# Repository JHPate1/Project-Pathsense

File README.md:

# PathSense

> Autonomous spatial awareness for the visually impaired. A light-weight, intelligent, vest-wearable vision for your environment.
(Tracked Via LAPSE)
https://stardance.hackclub.com/projects/27167
---

# WHAT IT IS

PathSense is a wearable computer vision navigation vest (HOLY JUMBLE OF WORDS) intended to provide users with a more confidence-gaining awareness of their surroundings. With a powerful Raspberry Pi 5 in its core, and a combined network of precise distance sensors and tactile & audio feedback, this vest allows individuals with any level of vision to traverse indoor and outdoor spaces alike.

(Note the hook on the back will be made with a type of plastic that bends in so it will behave more like a clip)
(I do not know the name of the plastic yet)

---

# HOW IT WORKS

Essentially, PathSense is a complex, sensor-fused computer vision system rather than having one single sensor that dictates what is occurring in an environment, it combines and merges data from multiple inputs, checking for consistency and using the interpreted data in a reliable way.

# THE SENSORS

For this system, we have established a network of:

- 4 Time-of-Flight (ToF) sensors: To continuously determine precise distances in 3 directions of the space around the user, to a range of 4 meters.

- an AI Camera: To assess higher level object detection of hazards, landmarks, obstacles and the immediate surrounding terrain.

- GPS Module: To provide general global location awareness, including basic route following and orientation in city blocks and street space awareness including side walk identification.

The raw output from these sensors is sent to the custom written Python backend which interprets things real time.

---
## System Architecture
```
+-------------------------------------+
|    Raspberry Pi 5                   |
+--------------+----------------------+
               |
    +----------+----------+
    |          |          |
+---v---+  +---v---+  +---v---+
| 4x ToF|  |AI Cam |  |  GPS  |
|Sensor |  | Feed  |  |Module |
+---+---+  +---+---+  +---+---+
    |          |          |
    +----------+----------+
               |
    +----------v----------+
    |  Custom Python Core |
    |  (Sensor Fusion &   |
    |   Decision Logic)   |
    +----------+----------+
               |
    +----------+----------+
    |          |          |
+---v---+            +---v---+
|3x     |            |Audio  |
|Haptic |            |Engine |
|Lines  |            |       |
+-------+            +-------+
```
---

---

## Core Subsystems

### Spatial Distance Mapping
Four ToF sensors continuously monitor the environment for physical boundaries. They track distances to nearby walls, furniture, curbs, and other obstacles, giving the system a raw but reliable depth map of what is directly around you.

### Contextual Computer Vision
The camera feed runs an object detection model (YOLO) that adds meaning to the raw distance data. It can tell the difference between a person and a pole, identify an upcoming staircase, or flag uneven terrain. This contextual layer is what turns numbers into useful information.

### Dynamic Ground Navigation
When you are outdoors, the GPS module works alongside the camera to evaluate ground layouts, identify sidewalk edges, and avoid rocky or uneven paths.

### Dual Channel Feedback
Spatial data is translated into vibrations across three haptic motors. The intensity and location of each pulse tell you where to go and what to avoid. When something needs your immediate attention, like a sudden drop or an oncoming cyclist, the audio engine cuts in with a clear and sharp voice alert along with the activation of all haptic motors.

---

## Smart Sensor Arbitration

Wearable sensor arrays have a classic problem: false positives caused by normal human movement. Walking swings your arms. Eating brings your hands near your chest. Without intelligence, these motions would trigger constant, useless alerts. PathSense solves this by treating the camera as the primary source of truth. When you move your arms into the sensor path, the object detection model recognizes your hands in real time. The Python core then automatically suppresses data from any ToF sensors that are currently blocked. The result: no false positives.

---

## Custom Hardware: The Pi 5 HAT

PathSense uses a custom designed Raspberry Pi 5 expansion HAT to keep the wearable robust and wearable friendly.

- Interface Consolidation: All GPIO pins are mapped to dedicated, keyed JST connector sockets. Every sensor, motor, and module plugs in cleanly and allows for easy repairs.
- Vibration Resistant Design: The connectors and layout are built to stay reliable even while you are walking, running (not recommended yet), or navigating bumpy terrain.
- Neat Form Factor: No loose wires, no breadboards, no cable spaghetti. Just a clean, integrated stack that fits comfortably inside the vest.

---

## Bill of Materials (BOM)

### Purchased Components

| Ref    | Component                              | Description                                                                                         | Qty | Unit Price            | Total        |
| ------ | -------------------------------------- | --------------------------------------------------------------------------------------------------- | --- | --------------------- | ------------ |
| RPI5   | Raspberry Pi 5/2GB                     | Raspberry Pi 5 Single Board Computer, 2GB RAM                                                       | 1   | \$65.00               | \$65.00      |
| TOF    | TOF400C VL53L1X                        | 4M Laser Ranging Sensor Module, TOF Time-of-Flight Distance, IIC Output, 4pcs                       | 1   | \$21.89               | \$21.89      |
| WIRE   | Fermerry 22AWG Stranded Wire           | 22AWG Stranded Wire Spool, 10ft Each, 6 Colors, Flexible Silicone Hook up Wire Kit, Tinned Copper   | 1   | \$12.29               | \$12.29      |
| GPS    | NEO-6M GPS Module                      | GPS Module Receiver, Navigation Satellite Positioning, with Antenna, High Sensitivity               | 1   | \$9.99                | \$9.99       |
| VEST   | JKSafety Hi Vis Reflective Safety Vest | Hi Vis Reflective Safety Vest with Pockets, Mesh Fabric, Construction Safety Apparel, Black, Size L | 1   | \$9.99                | \$9.99       |
| HAPTIC | HilBeliFU Vibration Motor Module       | DC5V 9000RPM Vibration Motor Module, PWM Control, for DIY/Wearable Smart Device, 3pcs               | 1   | \$7.65                | \$7.65       |
| CAM    | Arducam 5MP Camera for Raspberry Pi    | 5MP OV5647 Camera Module V1, 1080P HD, for Raspberry Pi 5/4/3/3B+                                   | 1   | \$6.99                | \$6.99       |
| PSU    | Raspberry Pi 5 Power Supply            | PD Adapter USB C, 5V 5A Power Adapter for Raspberry Pi 5                                            | 1   | \$11.99               | \$11.99      |
| CONN   | JST-XH 2.54mm Connector Kit            | 460Pcs JST-XH Connector Kit, 2.54mm Male/Female 2/3/4/5/6Pin Header Housing, Terminal Wires         | 1   | \$7.58                | \$7.58       |
|        |                                        |                                                                                                     |     | **Subtotal**          | **\$153.37** |
|        |                                        |                                                                                                     |     | **Shipping (Pishop)** | **\$11.51**  |
|        |                                        |                                                                                                     |     | **Shipping (Amazon)** | **\$0.00**   |
|        |                                        |                                                                                                     |     | **Tax (Pishop)**      | **\$3.45**   |
|        |                                        |                                                                                                     |     | **Tax (Amazon)**      | **\$4.69**   |
|        |                                        |                                                                                                     |     | **TOTAL**             | **\$173.02** |

### PCBWay

| Ref | Component | Description | Qty | Unit Price | Total |
|-----|-----------|-------------|-----|------------|-------|
| PCB | Custom Pi 5 HAT PCB | 2 layer, HASL finish, 1.6mm FR4 | 5 | $4.10 | $20.50 |

**Subtotal (PCBWay):** $FREE (grant)

### PCB Parts On Hand
All Pi Hat Connectors
**Subtotal (On Hand):** $0.00

### Cost Summary

| Category | Amount |
|----------|--------|
| Purchased Components | $173.02 |
| PCBWay (Custom HAT) | $00.00 |
| **Grand Total** | **$173.02** |

---

## Built With

- Raspberry Pi 5
- Python
- Time of Flight (ToF) distance sensors
- AI powered object detection
- Custom PCB HAT design
- Haptic motor drivers
- GPS positioning modules

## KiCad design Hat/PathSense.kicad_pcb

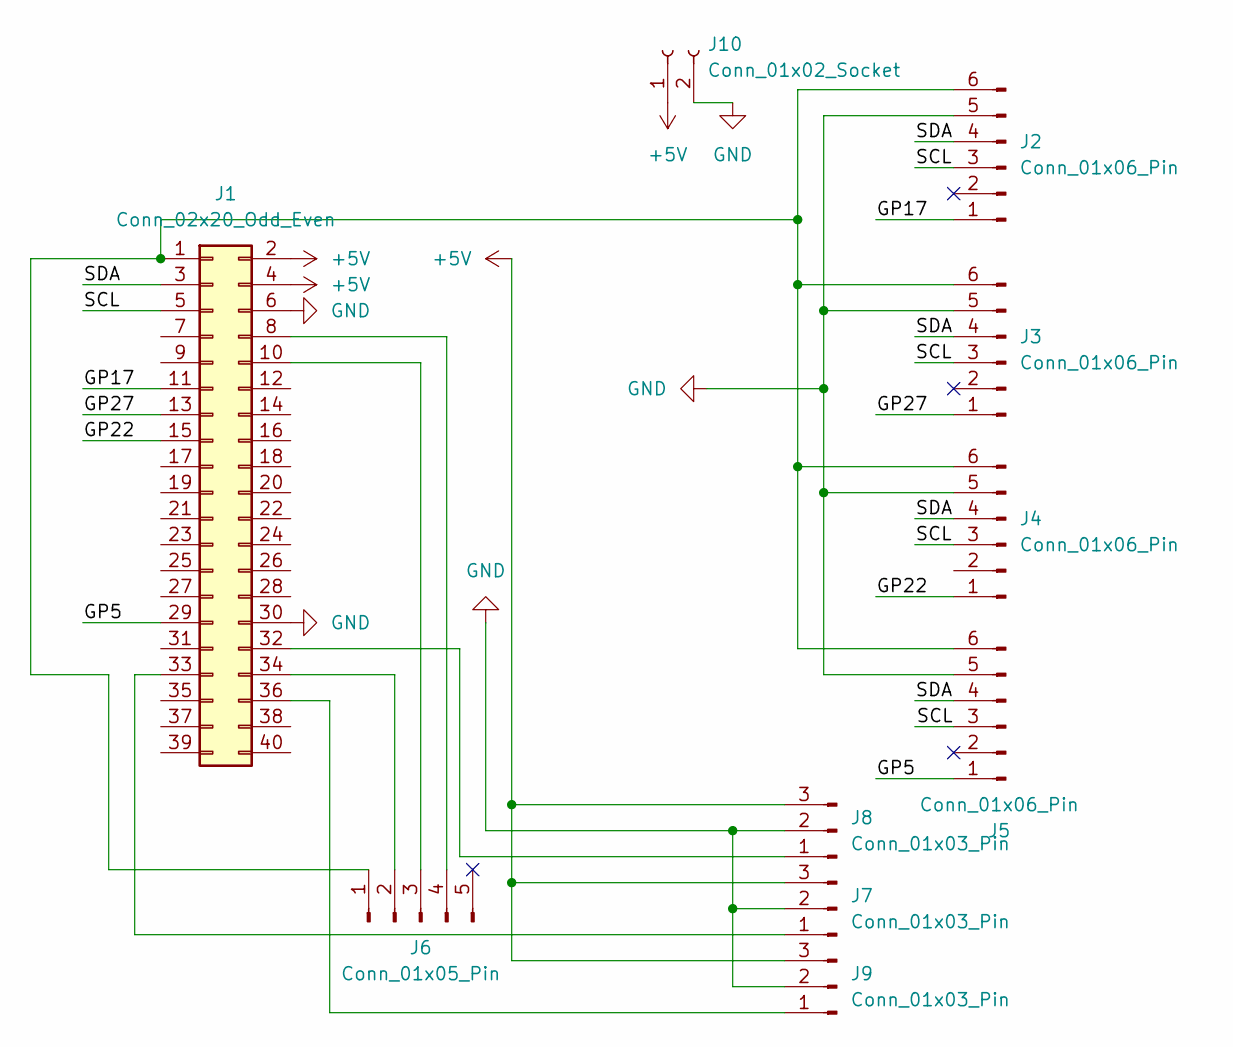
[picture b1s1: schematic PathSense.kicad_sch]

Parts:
J1: Conn_02x20_Odd_Even; PinSocket_2x20_P2.54mm_Vertical
J2, J3, J4, J5: Conn_01x06_Pin; PinHeader_1x06_P2.54mm_Vertical
J6: Conn_01x05_Pin; PinHeader_1x05_P2.54mm_Vertical
J7, J8, J9: Conn_01x03_Pin; PinHeader_1x03_P2.54mm_Vertical
J10: Conn_01x02_Socket; PinHeader_1x02_P2.54mm_Vertical

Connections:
+5V: J1.2, J1.4, J7.3, J8.3, J9.3, J10.1
/GP5: J1.29, J5.1
/GP17: J1.11, J2.1
/GP22: J1.15, J4.1
/GP27: J1.13, J3.1
/SCL: J1.5, J2.3, J3.3, J4.3, J5.3
/SDA: J1.3, J2.4, J3.4, J4.4, J5.4
GND: J1.6, J1.30, J2.5, J3.5, J4.5, J5.5, J7.2, J8.2, J9.2, J10.2
unnamed: J1.1, J2.6, J3.6, J4.6, J5.6, J6.1
unnamed: J1.8, J6.4
unnamed: J1.10, J6.3
unnamed: J1.32, J8.1
unnamed: J1.33, J7.1
unnamed: J1.34, J6.2
unnamed: J1.36, J9.1

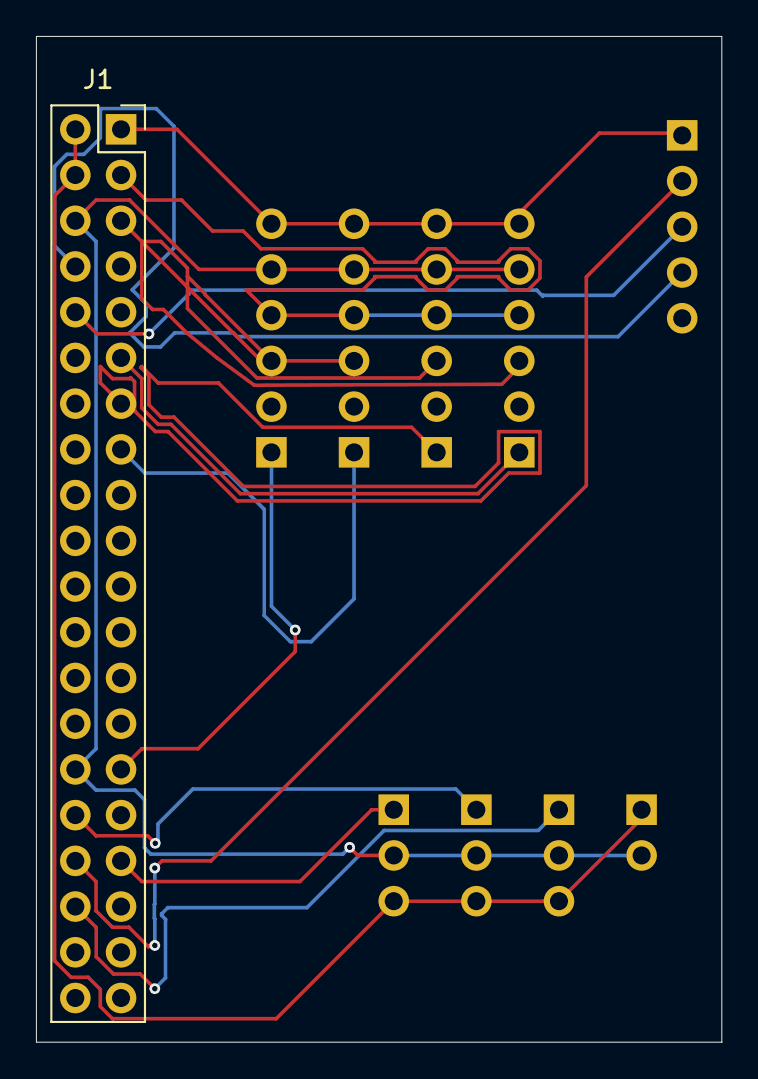
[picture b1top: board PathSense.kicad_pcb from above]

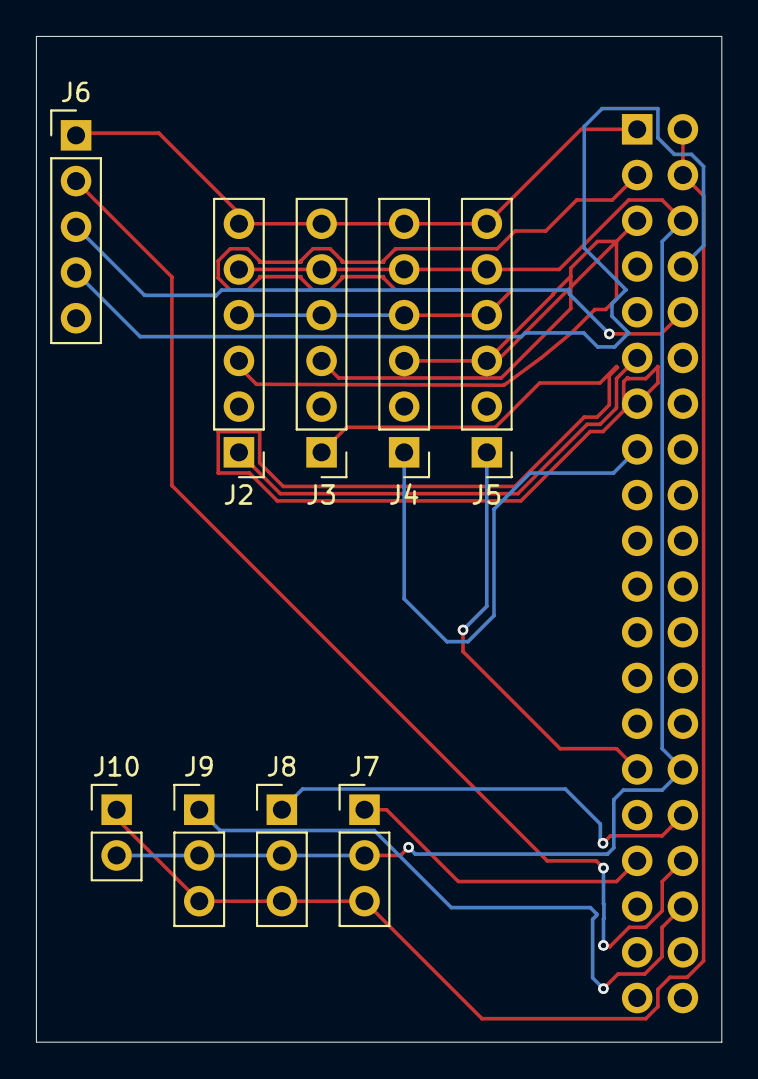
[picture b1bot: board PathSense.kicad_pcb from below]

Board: 2 copper layers, 38.1 x 55.9 mm, 10 parts (9 on the bottom side), 15 nets.

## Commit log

2026-06-27 Create temp
2026-06-27 Revise README with project details and structure
    Updated project name and expanded description. Added detailed sections on functionality, system architecture, core subsystems, and bill of materials.
2026-06-27 Create bom.csv with component details and costs
    Added bill of materials (BOM) with components and pricing.
2026-06-28 Revise README for clarity and improved descriptions
    Updated the README.md to improve clarity and structure, including rephrasing sections and enhancing descriptions of features and components.
2026-06-28 Remove feedback section from README
    Removed feedback section detailing haptic and audio alerts.
2026-06-29 Revise BOM and cost summary in README.md
    Updated the Bill of Materials (BOM) section with new components, quantities, and prices. Adjusted the cost summary to reflect the updated totals.
2026-06-29 Revise prices and complete missing data in BOM-1.csv
    Updated item prices and added missing values in BOM-1.csv.
2026-06-29 Revise BOM with updated component prices
    Updated the Bill of Materials (BOM) section with new pricing and components.
2026-06-29 Add images to README for visual reference
    Added images of PCB, schematic, and CAD designs to the README.
2026-06-29 Update README with LAPSE tracking details
    Add LAPSE tracking information and project link.
